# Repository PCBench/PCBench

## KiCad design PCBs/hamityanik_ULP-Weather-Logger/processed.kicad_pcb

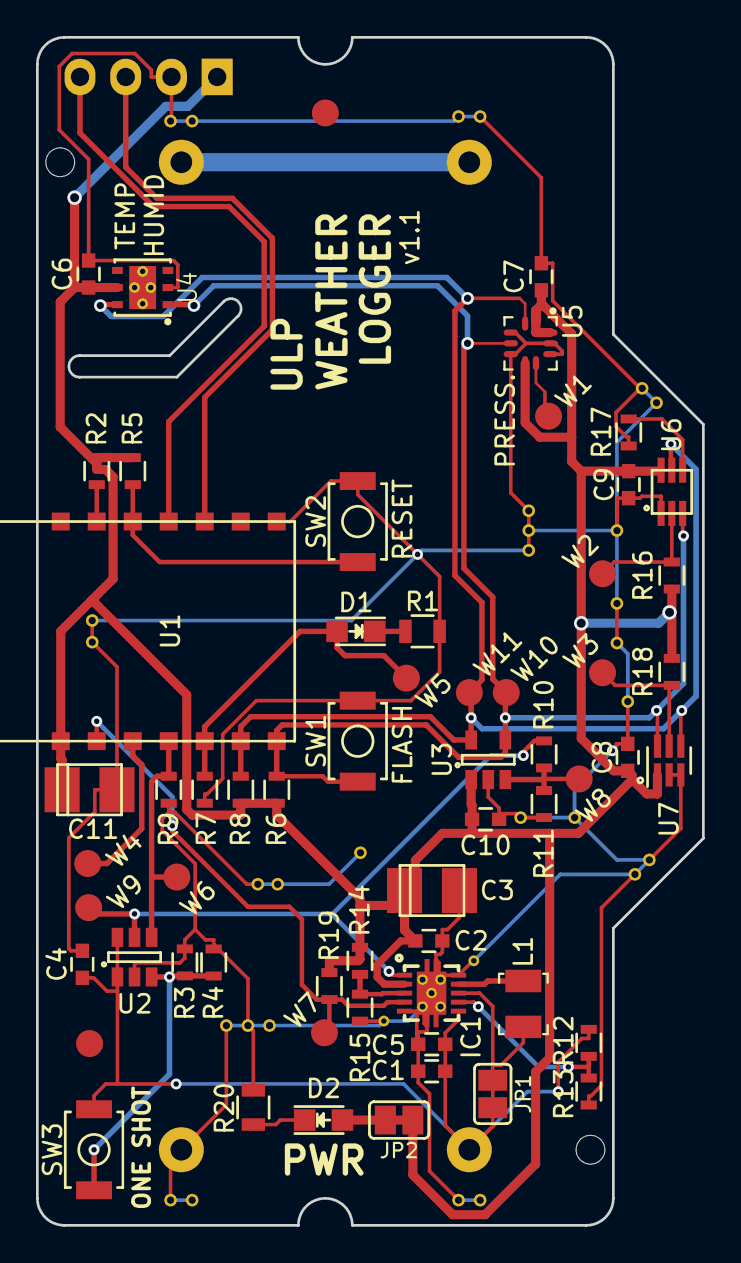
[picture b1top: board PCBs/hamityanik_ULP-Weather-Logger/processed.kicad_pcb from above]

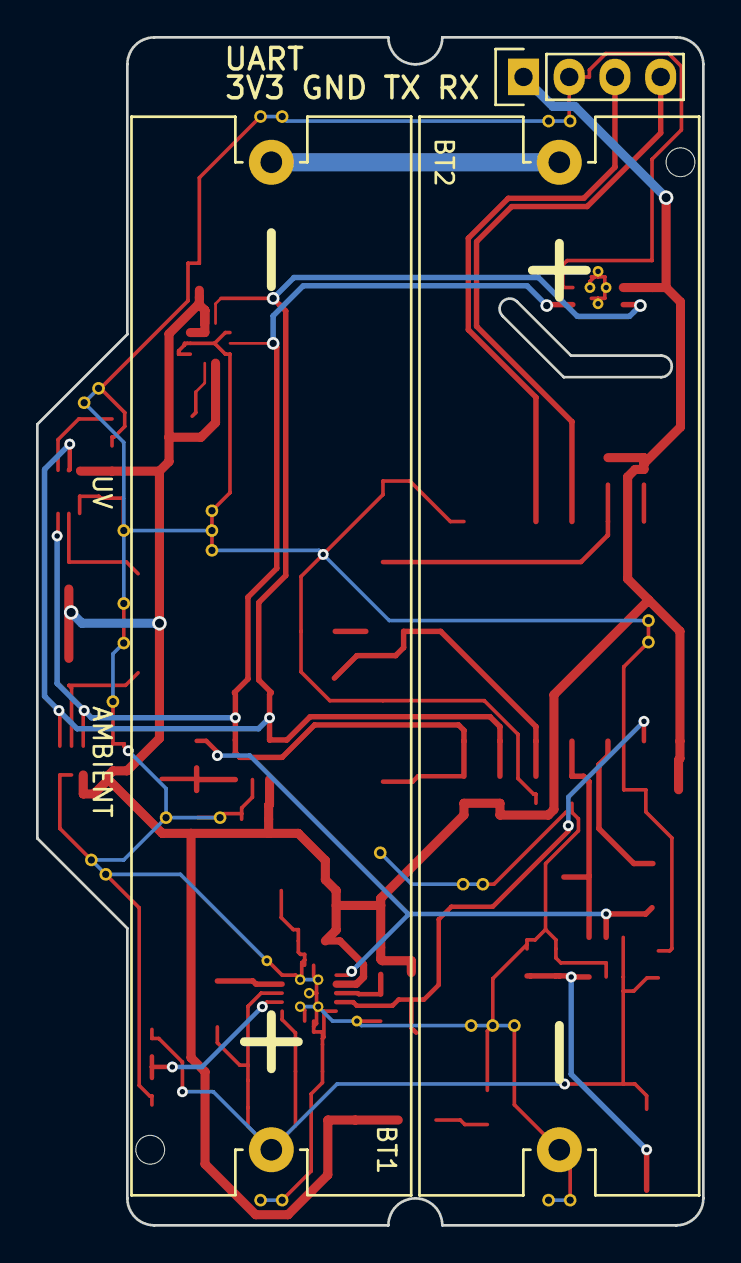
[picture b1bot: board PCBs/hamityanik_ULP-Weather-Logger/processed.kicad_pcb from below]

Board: 2 copper layers, 37.0 x 66.0 mm, 63 parts (3 on the bottom side), 26 nets.

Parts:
BT1, BT2: 1015; Keystone_1015_Holder_Battery_AA
C1: 10uF; C_0603
C2: 2.2uF; C_0603
C3: 100uF; TantalC_SizeB_EIA-3528_Reflow
C4, C5, C6, C7, C8, C9, C10: 0.1uF; C_0603
C11: DNP; TantalC_SizeB_EIA-3528_Reflow
D1, D2: LTST-C170KRKT; LED_0805
FID1, FID2: FIDUCIAL; Fiducial
IC1: TPS61025; TI_DRC_S-PVSON-N10
JP1, JP2: JUMPER; SJ_OPEN
L1: 6.8uH; Inductor_1210
P1: CONN_01X04; Pin_Header_Straight_1x04
R1, R20: 1k; R_0805
R2, R13, R14: 0R; R_0603
R3: 140k; R_0603
R4: 174k; R_0603
R5, R6, R7, R8, R9, R16, R18: 10k; R_0603
R10: 1k; R_0603
R11: 390k; R_0603
R12, R15: DNP; R_0603
R17: 270k; R_0603
R19: 1M; R_0603
SW1, SW2, SW3: PTS820 J15M SMTR LFS; Tact_Switch_Top_PTS820
U1: ESP8266-ESP-03
U2: TPL5111; SOT-23-6
U3: MCP3021; SOT-23-5
U4: HDC1080; WSON-6-PAD
U5: LPS25HB; ST_LPS25HB
U6: VEML6070; OPLGA6
U7: TSL2561; WDFN-6_2x2mm_Pitch0.65mm
W1: PRES_INT; Measurement_Point_Round-SMD-Pad_Small
W2: UV_INT; Measurement_Point_Round-SMD-Pad_Small
W3: AMB_INT; Measurement_Point_Round-SMD-Pad_Small
W4: GPIO_12; Measurement_Point_Round-SMD-Pad_Small
W5: L; Measurement_Point_Round-SMD-Pad_Small
W6: DONE; Measurement_Point_Round-SMD-Pad_Small
W7: LOWBATT; Measurement_Point_Round-SMD-Pad_Small
W8: BATT_VOUT; Measurement_Point_Round-SMD-Pad_Small
W9: DRVn; Measurement_Point_Round-SMD-Pad_Small
W10: SDA; Measurement_Point_Round-SMD-Pad_Small
W11: SCL; Measurement_Point_Round-SMD-Pad_Small

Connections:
+3V3: C2.1, C3.1, C6.1, C7.1, C8.1, C9.1, C10.1, C11.1, D2.2, IC1.2, JP2.1, JP2.2, P1.1, R2.1, R5.1, R6.1, R8.1, R14.1, R16.1, R18.1, R19.1, U1.8, U3.1, U4.5, U5.1, U5.6, U5.10, U6.6, U7.1
+BATT: BT1.1, C1.1, C4.1, C5.1, IC1.6, IC1.8, JP1.1, JP1.2, L1.1, R12.1, SW3.1, U2.1, U2.6
/BATT_VOUT: R10.2, R11.1, U3.3, W8.1
/DONE: R9.1, U1.11, U2.4, W6.1
/DRVn: IC1.1, R10.1, U2.5, W9.1
/FB: IC1.3, R14.2, R15.1
/GPIO_12: U1.10, W4.1
/L: D1.2, R7.1, U1.12, W5.1
/LBI: IC1.7, R12.2, R13.1
/LOWBATT: IC1.4, R19.2, U1.9, W7.1
/M_DRV: R3.1, R4.1, SW3.2, U2.3
/RX: P1.4, U1.4
/SCL: R8.2, U1.13, U3.5, U4.6, U5.2, U6.5, U7.4, W11.1
/SDA: R6.2, SW1.1, U1.14, U3.4, U4.1, U5.4, U6.3, U7.6, W10.1
/TX: P1.3, U1.3
GND: BT2.2, C1.2, C2.2, C3.2, C4.2, C5.2, C6.2, C7.2, C8.2, C9.2, C10.2, C11.2, IC1.0, IC1.5, IC1.10, P1.2, R1.2, R3.2, R4.2, R7.2, R9.2, R11.2, R13.2, R15.2, R17.1, R20.2, SW1.2, SW2.2, U1.1, U2.2, U3.2, U4.2, U5.3, U5.5, U5.8, U5.9, U6.1, U7.2, U7.3
unnamed: BT1.2, BT2.1
unnamed: D1.1, R1.1
unnamed: D2.1, R20.1
unnamed: IC1.9, L1.2
unnamed: R2.2, U1.6
unnamed: R5.2, SW2.1, U1.5
unnamed: R16.2, U6.2, W2.1
unnamed: R17.2, U6.4
unnamed: R18.2, U7.5, W3.1
unnamed: U5.7, W1.1

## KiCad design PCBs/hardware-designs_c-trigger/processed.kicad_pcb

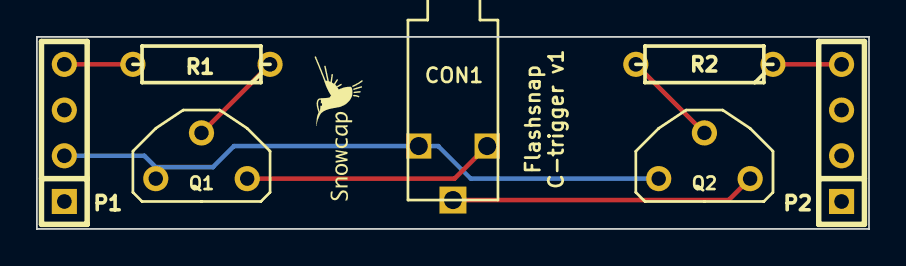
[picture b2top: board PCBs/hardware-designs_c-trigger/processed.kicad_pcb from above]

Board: 2 copper layers, 46.2 x 10.7 mm, 8 parts (0 on the bottom side), 7 nets.

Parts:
CON1: BARREL_JACK; SJ2.5PC
P1, P2: CONN_4; SIL-4
Q1, Q2: NPN; TO92PN-LARGE
R1, R2: R; R3
VAL: REF; LOGO_SNOWCAP_FRONT_SMALL

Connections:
unnamed: CON1.1, P1.2, Q1.1, Q2.1
unnamed: CON1.2, Q1.3
unnamed: CON1.3, Q2.3
unnamed: Q2.2, R2.2
unnamed: Q1.2, R1.1
unnamed: P1.4, R1.2
unnamed: P2.4, R2.1

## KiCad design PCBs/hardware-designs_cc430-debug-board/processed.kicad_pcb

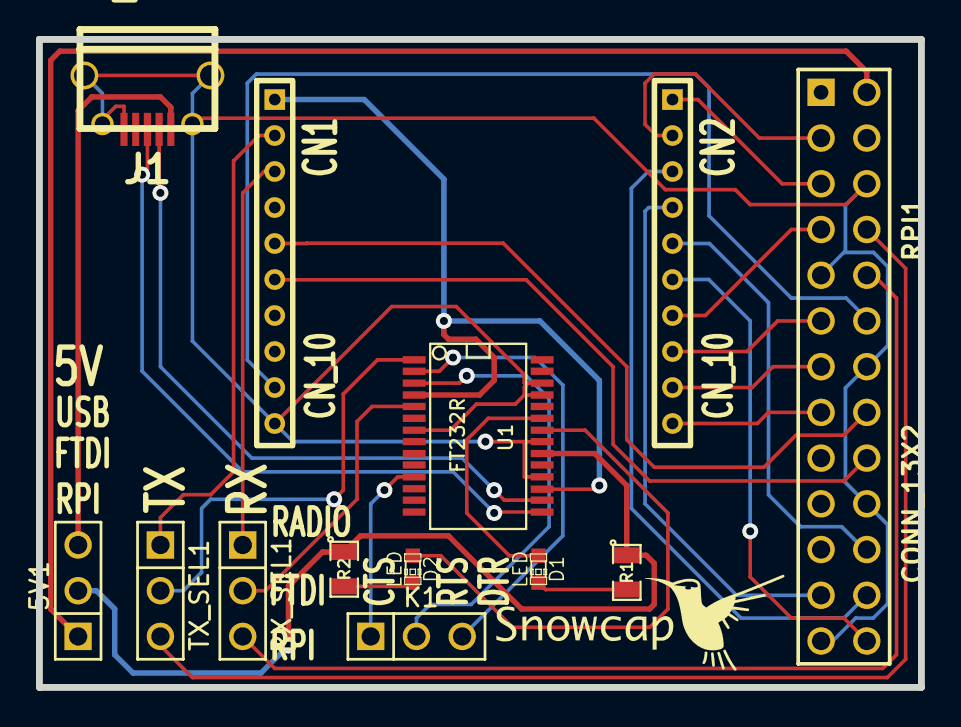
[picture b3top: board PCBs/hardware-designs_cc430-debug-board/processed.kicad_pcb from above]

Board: 2 copper layers, 49.0 x 36.0 mm, 14 parts (0 on the bottom side), 33 nets.

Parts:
5V1: CN_3; PIN_ARRAY_3X1
CN1, CN2: CN_10; CONN-10-2MM
D1, D2: LED; LED-0603
J1: USB_MICRO; USB_MICRO_10118194-0001LF
K1: CONN_3; PIN_ARRAY_3X1
Noname_1: LOGO_SNOWCAP_FRONT
R1, R2: 500R; SM0805
RPI1: CONN_13X2; pin_array_13x2
RX_SEL1: CN_3; PIN_ARRAY_3X1
TX_SEL1: CN_3; PIN_ARRAY_3X1
U1: FT232R; SSOP28

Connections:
+3.3V: CN1.1, U1.4, U1.17
+5V: 5V1.2, R1.1, R2.1, U1.20
/RADIO_A0: CN2.8, RPI1.11
/RADIO_A0_SCLK: CN2.4, RPI1.23
/RADIO_A0_SS: CN2.3, RPI1.24
/RADIO_A1: CN2.9, RPI1.13
/RADIO_A2: CN2.10, RPI1.15
/RADIO_A3: CN1.9, RPI1.12
/RADIO_ACLK: CN2.5, RPI1.22
/RADIO_B0_SCL: CN2.1, RPI1.5
/RADIO_B0_SDA: CN2.2, RPI1.3
/RADIO_NRST: CN1.5, RPI1.16
/RADIO_RFGDO0: CN2.7, RPI1.7
/RADIO_RFGDO2: CN2.6, RPI1.26
/RADIO_RX: CN1.3, RX_SEL1.1
/RADIO_TEST: CN1.6, RPI1.18
/RADIO_TX: CN1.2, TX_SEL1.1
/RPI_RX: RPI1.10, RX_SEL1.3
/RPI_TX: RPI1.8, TX_SEL1.3
GND: CN1.10, J1.5, J1.6, J1.7, J1.8, J1.9, RPI1.6, RPI1.9, RPI1.14, RPI1.20, RPI1.25, U1.7, U1.18, U1.21, U1.25, U1.26
unnamed: RX_SEL1.2, U1.5
unnamed: TX_SEL1.2, U1.1
unnamed: D1.1, U1.23
unnamed: J1.3, U1.15
unnamed: K1.1, U1.11
unnamed: K1.2, U1.3
unnamed: K1.3, U1.2
unnamed: 5V1.1, RPI1.2
unnamed: 5V1.3, J1.1
unnamed: J1.2, U1.16
unnamed: D2.2, R2.2
unnamed: D1.2, R1.2
unnamed: D2.1, U1.22

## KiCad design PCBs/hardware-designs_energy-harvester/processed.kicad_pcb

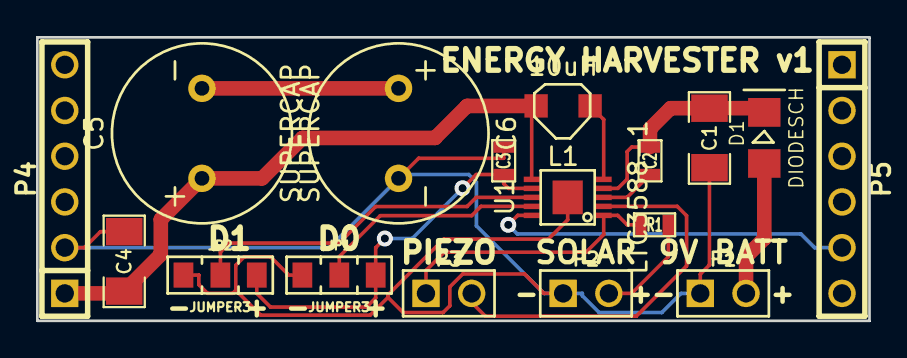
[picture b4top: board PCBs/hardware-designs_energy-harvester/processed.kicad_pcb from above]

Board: 2 copper layers, 46.2 x 15.7 mm, 18 parts (1 on the bottom side), 14 nets.

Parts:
C1: 100uF; SM1206
C2: 1uF; SM0603
C3: 4.7uF; SM0603
C4: 10uF; SM1206
C5, C6: SUPERCAP; SUPERCAP_ESHSR-0010C0-002R7
D1: DIODESCH; DIODE-1206
JP1, JP2: JUMPER3; SM0805_JUMPER3
L1: 10uH; INDUCTOR-CDRH2D18-LD
Noname_1: LOGO_SNOWCAP_BACK
P1, P2, P3: CONN_2; PIN_ARRAY_2X1
P4, P5: CONN_6; PIN_ARRAY-6X1
R1: 300R; SM0603
U1: LTC3588-1; LTC3588-1-MSOP10

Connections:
/PGOOD: P5.5, U1.10
/VIN2: C3.1, JP1.3, JP2.3, U1.7
GND: C1.2, C3.2, C4.2, C6.2, JP1.1, JP2.1, P1.1, P2.1, P4.2, U1.11
unnamed: P3.1, R1.2, U1.1
unnamed: P3.2, U1.2
unnamed: JP2.2, U1.8
unnamed: C5.2, C6.1
unnamed: JP1.2, U1.9
unnamed: D1.1, P1.2
unnamed: C2.2, U1.3
unnamed: P2.2, R1.1
unnamed: L1.1, U1.5
unnamed: C1.1, C2.1, D1.2, U1.4
VCC: C4.1, C5.1, L1.2, P4.1, U1.6

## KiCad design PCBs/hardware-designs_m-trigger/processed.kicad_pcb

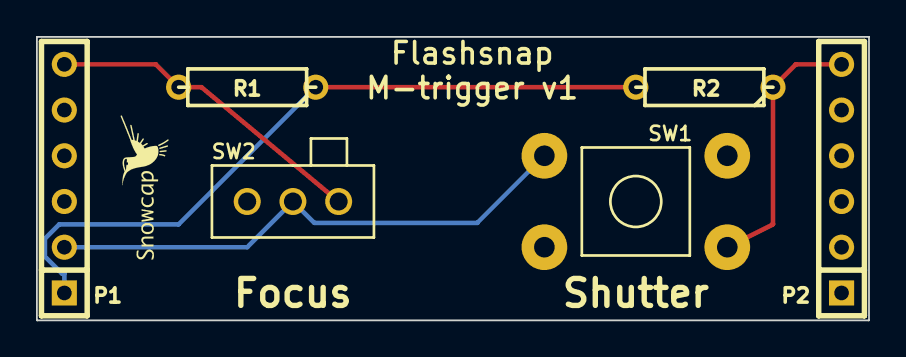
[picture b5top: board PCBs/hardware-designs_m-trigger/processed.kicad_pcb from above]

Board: 2 copper layers, 46.2 x 15.7 mm, 7 parts (0 on the bottom side), 4 nets.

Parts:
P1, P2: CONN_6; SIL-6
R1, R2: R; R3
SW1: SW_PUSH; SW_PUSH_6MM
SW2: DUAL_SWITCH_INV; SLIDE_SWITCH
VAL: REF; LOGO_SNOWCAP_FRONT_SMALL

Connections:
unnamed: P1.6, R1.2, SW2.1
unnamed: P2.6, R2.1, SW1.2
unnamed: P1.2, SW1.1, SW2.2
unnamed: P1.1, R1.1, R2.2

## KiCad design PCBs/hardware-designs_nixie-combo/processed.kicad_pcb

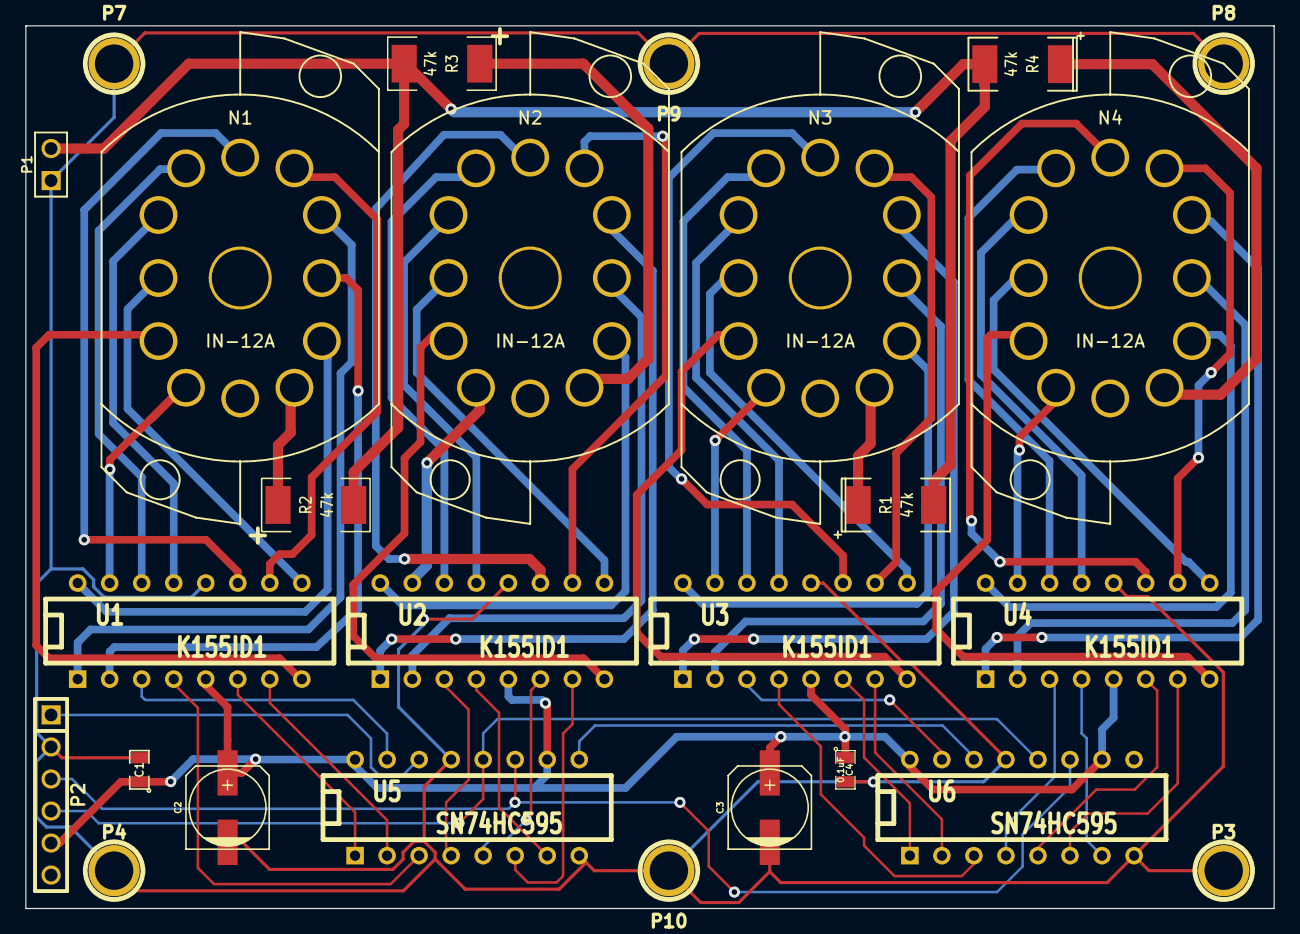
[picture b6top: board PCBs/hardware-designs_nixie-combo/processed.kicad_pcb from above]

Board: 2 copper layers, 99.0 x 70.0 mm, 27 parts (1 on the bottom side), 67 nets.

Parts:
C1, C4: 0.1uF; SM0805
C2, C3: 100uF; c_elec_6.3x7.7
N1, N2, N3, N4: IN-12A; IN-12A-SOCKET
Noname_1: LOGO_SNOWCAP_BACK
P1: CONN_2; PIN_ARRAY_2X1
P2: CONN_6; PIN_ARRAY-6X1
P3, P4, P7, P8, P9, P10: CONN_1; 1pin
R1, R2, R3, R4: 47k; SM2512
U1, U2, U3, U4: K155ID1; DIP-16__300
U5, U6: SN74HC595; DIP-16__300

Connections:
+3.3V: C1.1, C2.1, C3.1, C4.1, P2.5, U1.5, U2.5, U3.5, U4.5, U5.10, U5.16, U6.10, U6.16
/a0: N1.2, U1.16
/a1: N1.11, U1.15
/a2: N1.10, U1.8
/a3: N1.9, U1.9
/a4: N1.8, U1.13
/a5: N1.7, U1.14
/a6: N1.6, U1.11
/a7: N1.5, U1.10
/a8: N1.4, U1.1
/a9: N1.3, U1.2
/b0: N2.2, U2.16
/b1: N2.11, U2.15
/b2: N2.10, U2.8
/b3: N2.9, U2.9
/b4: N2.8, U2.13
/b5: N2.7, U2.14
/b6: N2.6, U2.11
/b7: N2.5, U2.10
/b8: N2.4, U2.1
/b9: N2.3, U2.2
/c0: N3.2, U3.16
/c1: N3.11, U3.15
/c2: N3.10, U3.8
/c3: N3.9, U3.9
/c4: N3.8, U3.13
/c5: N3.7, U3.14
/c6: N3.6, U3.11
/c7: N3.5, U3.10
/c8: N3.4, U3.1
/c9: N3.3, U3.2
/d0: N4.2, U4.16
/d1: N4.11, U4.15
/d2: N4.10, U4.8
/d3: N4.9, U4.9
/d4: N4.8, U4.13
/d5: N4.7, U4.14
/d6: N4.6, U4.11
/d7: N4.5, U4.10
/d8: N4.4, U4.1
/d9: N4.3, U4.2
GND: C1.2, C2.2, C3.2, C4.2, P1.1, P2.2, P3.1, P4.1, P7.1, P8.1, P9.1, P10.1, U1.12, U2.12, U3.12, U4.12, U5.8, U5.13, U6.8, U6.13
HT: P1.2, R1.2, R2.2, R3.2, R4.2
unnamed: N4.1, R4.1
unnamed: U4.7, U6.6
unnamed: U4.4, U6.7
unnamed: U4.3, U6.4
unnamed: U3.7, U6.2
unnamed: U3.6, U6.1
unnamed: U3.4, U6.3
unnamed: N1.1, R2.1
unnamed: N2.1, R3.1
unnamed: N3.1, R1.1
unnamed: U3.3, U6.15
unnamed: U4.6, U6.5
unnamed: U5.9, U6.14
unnamed: P2.4, U5.12, U6.12
unnamed: P2.3, U5.11, U6.11
unnamed: P2.1, U5.14
unnamed: U2.4, U5.7
unnamed: U2.7, U5.6
unnamed: U2.6, U5.5
unnamed: U2.3, U5.4
unnamed: U1.4, U5.3
unnamed: U1.7, U5.2
unnamed: U1.6, U5.1
unnamed: U1.3, U5.15

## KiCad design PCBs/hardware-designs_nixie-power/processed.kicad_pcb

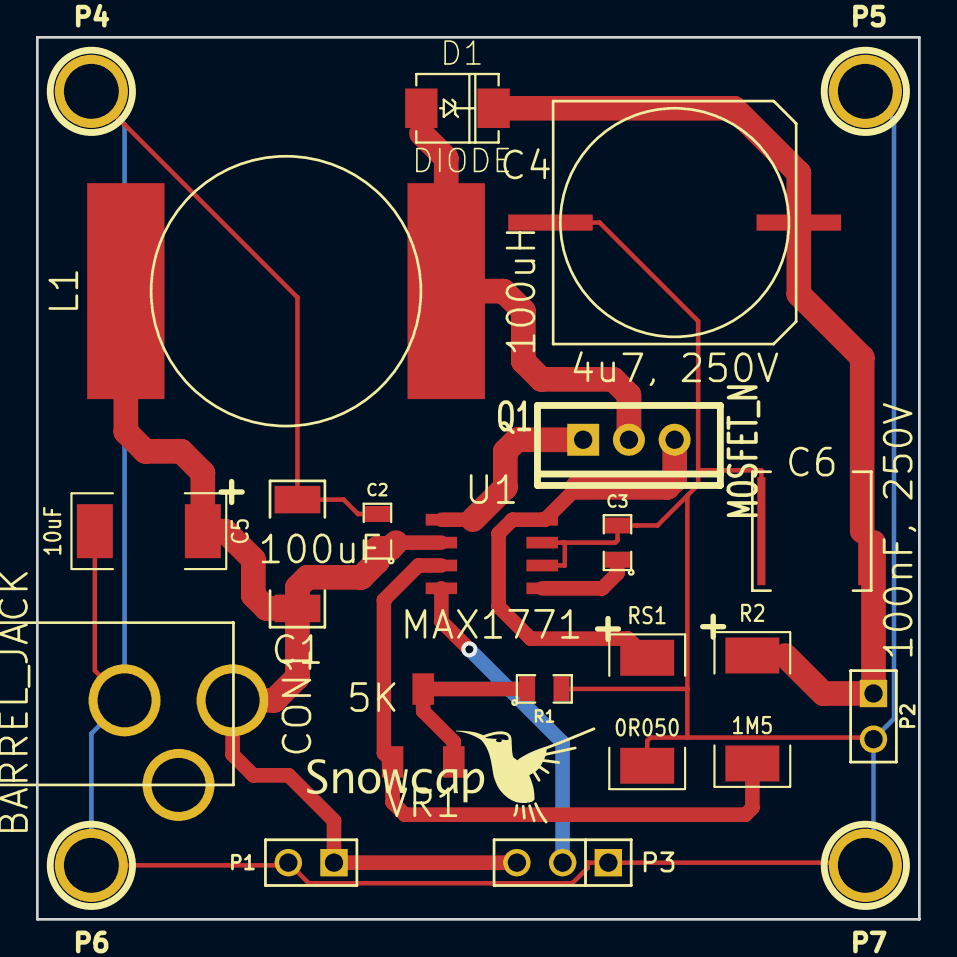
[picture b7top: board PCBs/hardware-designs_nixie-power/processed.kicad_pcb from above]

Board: 2 copper layers, 49.0 x 49.0 mm, 24 parts (1 on the bottom side), 10 nets.

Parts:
C1: 100uF; SM2917
C2, C3: 100nF; SM0805
C4: 4u7, 250V; c_elec_13.5x13.8
C5: 10uF; SM2512
C6: 100nF, 250V; SM2420_fc1
CON1: BARREL_JACK; BARREL_JACK-PJ-002AH
D1: DIODE; DO214
L1: 100uH; UNI-PAC4B
Noname_1: LOGO_SNOWCAP_BACK
Noname_2: LOGO_SNOWCAP_FRONT
P1, P2: CONN_2; PIN_ARRAY_2X1
P3: CONN_3; PIN_ARRAY_3X1
P4, P5, P6, P7: CONN_1; 1pin
Q1: MOSFET_N; TO220_VERT_GDS
R1: 10K; SM0805
R2: 1M5; SM2512
RS1: 0R050; SM2512
U1: MAX1771; SOIC-8
VR1: 5K; 3314S-TRIMPOT

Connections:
FB: R2.2, U1.3, VR1.1
GND: C1.2, C2.2, C3.2, C4.2, C5.2, C6.2, CON1.2, P1.2, P2.2, P3.1, P4.1, P5.1, P6.1, P7.1, R1.2, RS1.2, U1.6, U1.7
unnamed: C3.1, U1.5
unnamed: C1.1, C2.1, C5.1, CON1.1, L1.1, P1.1, P3.3, U1.2
unnamed: Q1.G, U1.1
unnamed: C4.1, C6.1, D1.2, P2.1, R2.1
unnamed: Q1.S, RS1.1, U1.8
unnamed: P3.2, U1.4
unnamed: D1.1, L1.2, Q1.D
unnamed: R1.1, VR1.2, VR1.3
